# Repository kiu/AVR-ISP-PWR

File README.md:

# AVR-ISP-PWR

Simple AVR ISP breakout to inject power from a lab supply

# License

This project is licensed under the Creative Commons Attribution-NonCommercial 3.0 Unported (CC BY-NC 3.0) license.

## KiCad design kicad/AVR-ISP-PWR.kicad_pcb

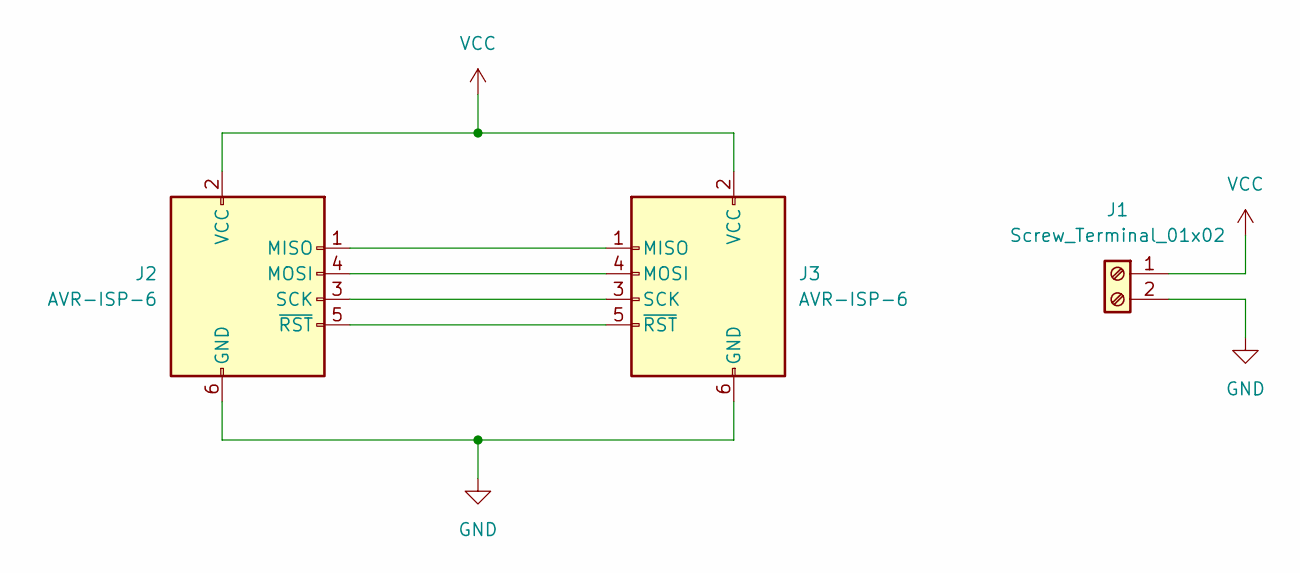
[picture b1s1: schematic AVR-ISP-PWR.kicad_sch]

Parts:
J1: Screw_Terminal_01x02; TerminalBlock_RND_205-00287_1x02_P5.08mm_Horizontal
J2, J3: AVR-ISP-6; IDC-Header_2x03_P2.54mm_Vertical

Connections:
GND: J1.2, J2.6 (GND), J3.6 (GND)
unnamed: J2.1 (MISO), J3.1 (MISO)
unnamed: J2.4 (MOSI), J3.4 (MOSI)
unnamed: J2.3 (SCK), J3.3 (SCK)
unnamed: J2.5 (~RST), J3.5 (~RST)
VCC: J1.1, J2.2 (VCC), J3.2 (VCC)

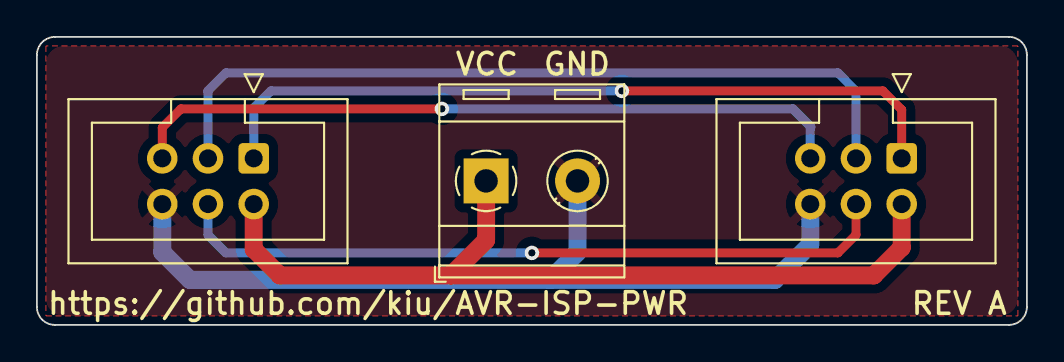
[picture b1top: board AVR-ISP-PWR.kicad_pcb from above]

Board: 2 copper layers, 55.0 x 16.0 mm, 3 parts (0 on the bottom side), 6 nets.
